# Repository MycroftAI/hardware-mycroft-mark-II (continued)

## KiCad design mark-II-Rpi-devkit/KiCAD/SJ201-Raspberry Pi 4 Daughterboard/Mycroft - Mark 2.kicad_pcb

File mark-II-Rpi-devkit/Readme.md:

# Mycroft Mark II - Prototype Printed Circuit Board

*⛵️ Note that this repository is a work-in-progress. It will be updated and improved on over time.*

This is the first prototype design for the Mark II daughterboard PCB (SJ201).

This board interfaces directly to the Raspberry Pi 4 via the 40-pin GPIO adding a high-quality speaker and microphone array, as well as LEDs and hardware inputs for non-voice interaction and feedback.

The SJ201 can also be used as a USB microphone array with barge-in support. In this configuration the amplifiers do not work as the USB port cannot supply the required power.

The part number SJ201 is derived from Mike’s “Simon Jester” alias in “The Moon is a Harsh Mistress”.

## Major Components
* USB Soundcard (PCM2706)
* Audio Front End (XMOS XVF-3510) - for Microphone input processing
* 20W Amplifier (Maxim Integrated MAX9744)
* 2 Digital MEMS Microphones (ST Micro MP34DT05)
* 12 RGB LEDs (WorldSemi WS2813-MINI)
* 3 momentary buttons (volume up, volume down, action)
* 1 toggle switch (mic mute)

## New Form Factor
There is a new form factor for the Mark II. The new form matches the simplicity to our approach to SJ201 daughterboard. The blocking of the major components is found within the MkII Blocking r2.zip. 

## Our open hardware principles
* **Copy our designs** – build your own Mycroft Mark 2 - Raspberry Pi Edition or its individual parts
* **Modify our designs** – remixing is encouraged
* **Sell products based on our designs** – commercial use is permitted
* **Always keep the open license** – contribute your output back to the community
* **Credit the original author(s)** – like they do in science

## Technical Documentation
For technical details of this board see the [SJ201-Datasheet](SJ201-Datasheet.md).

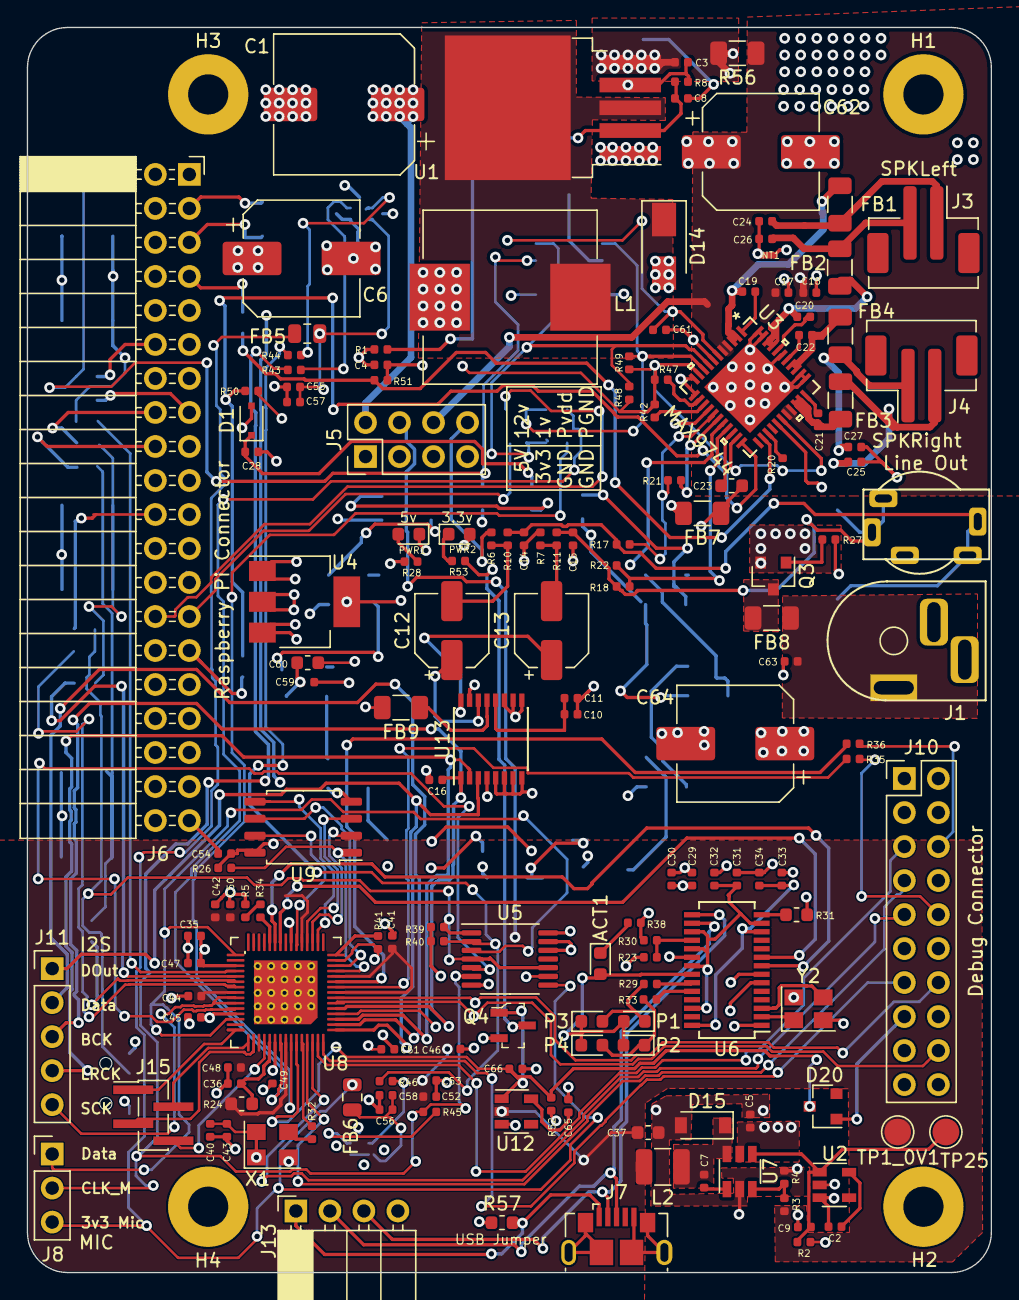
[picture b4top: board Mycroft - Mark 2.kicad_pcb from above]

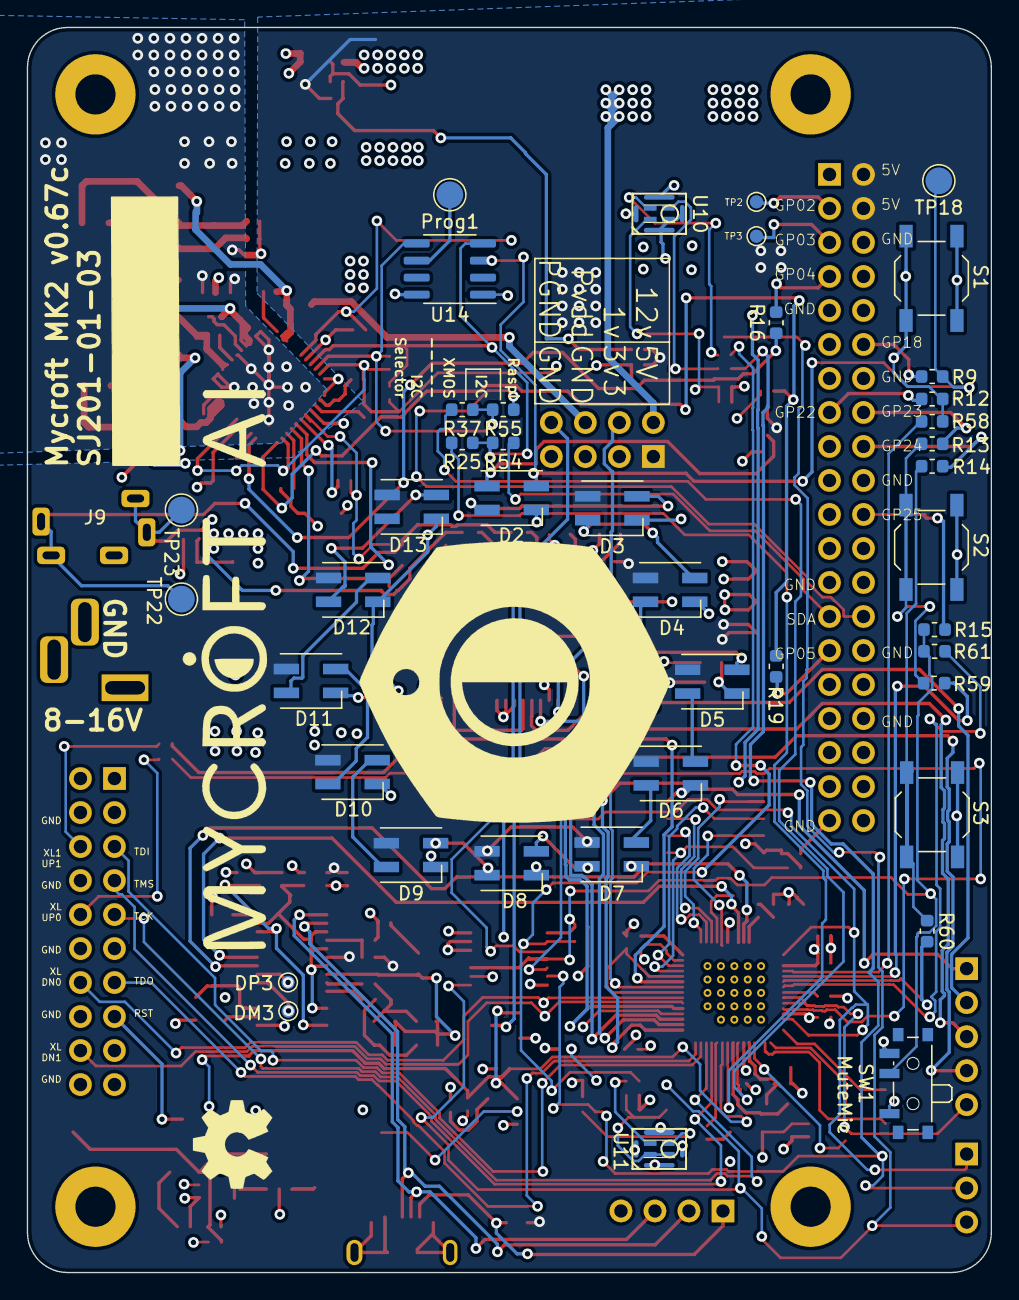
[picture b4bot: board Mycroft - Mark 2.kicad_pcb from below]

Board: 4 copper layers, 72.0 x 93.0 mm, 211 parts (46 on the bottom side), 152 nets.

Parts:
ACT1: LED; LED_0603_1608Metric
C1: 220uF/50V; CP_Elec_10x10
C2, C65: 2.2NF; C_0402_1005Metric
C3, C4, C55, C56, C61: 1uF; C_0402_1005Metric
C5, C11, C30, C32, C34, C59: 10UF; C_0402_1005Metric
C6: 330uF/25V; CP_Elec_8x10.5
C7, C14, C15: 10nF; C_0402_1005Metric
C8: 33NF; C_0402_1005Metric
C9, C66: 1NF; C_0402_1005Metric
C10, C17, C18, C19, C20, C21, C22, C28, C29, C31, C33, C35, C36, C40, C41, C42, C43, C44, C45, C46, C47, C48, C49, C50, C51, C52, C53, C54, C57, C58, C63: 100NF; C_0402_1005Metric
C12, C13: 47UF/16V; CP_Elec_5x5.3
C16: 22pFDNP; C_0402_1005Metric
C23: 2.2UF; C_0603_1608Metric
C24, C25, C26, C27: 470pF; C_0402_1005Metric
C37, C60: 22UF; C_0603_1608Metric
C62, C64: 470UF/16V; CP_Elec_8x10.5
D1: 250mA/100V; D_SOD-323F
D2, D3, D4, D5, D6, D7, D8, D9, D10, D11, D12, D13: WS2812B; LED_WS2812_Mini_3.5x3.5mm_P1.1mm
D14: D_Schottky; D_SMA
D15: D_Schottky; D_SOD-123
D20: BAT54A; SOT-23
DM3: TestPoint; TestPoint_Pad_D1.0mm
DP3: TestPoint; TestPoint_Pad_D1.0mm
FB1, FB2, FB3, FB4, FB7, FB8, FB9: FB; R_1206_3216Metric
FB5, FB6: 1000R; R_0805_2012Metric
H1, H2, H3, H4: MountingHole; MountingHole_3mm_Pad
H5: MountingHole; mycroft_logo_graphic
H6: MountingHole; OSHW-Symbol_6.7x6mm_SilkScreen
H7: MountingHole; mycroft_logo_words
J1: Barrel_Jack; BarrelJack_Vertical
J3, J4: SPK; JST_PH_B2B-PH-SM4-TB_1x02-1MP_P2.00mm_Vertical
J5: PowerTP; PinHeader_2x04_P2.54mm_Vertical
J6: Raspberry_Pi_4; PinSocket_2x20_P2.54mm_Horizontal
J7: USB_B_Micro; USB_Micro-B_GCT_USB3076-30-A
J8: MIC; PinHeader_1x03_P2.54mm_Vertical
J9: AudioJack3_Ground_Switch; STX-3790-5N
J10: Debug Connector; PinHeader_2x10_P2.54mm_Vertical
J11: I2S; PinHeader_1x05_P2.54mm_Vertical
J13: USB-PinHeader; PinSocket_1x04_P2.54mm_Horizontal
J15: Output; PinHeader_1x04_P1.27mm_Vertical_SMD_Pin1Left
L1: 47uH; L_Wuerth_HCI-1365
L2: 2.2UH ±30% 1.55A; L_1210_3225Metric
NT1: Net-Tie_2; NetTie-2_SMD_Pad0.5mm
P1, P2, P3, P4: LED; LED_0603_1608Metric
PWR1, PWR2: LED_RED; LED_0603_1608Metric
Prog1: Prog; TestPoint_Pad_D2.0mm
Q3: AO3401A; SOT-23
Q4: 2N7002; SOT-23-3
R1, R2, R20, R39, R42, R47, R48, R49, R50, R51, R52: 10k; R_0402_1005Metric
R3: 75k; R_0402_1005Metric
R4: 330K; R_0402_1005Metric
R5: 10R; R_0402_1005Metric
R6, R7: 220k; R_0402_1005Metric
R8: 3.3K; R_0402_1005Metric
R9, R12, R13, R14, R15, R16, R19, R54, R55: 0R; R_0603_1608Metric
R10, R11, R43, R44, R45, R46: 100R; R_0402_1005Metric
R17, R18, R21, R22: 20k; R_0402_1005Metric
R23, R26, R40: 47K; R_0402_1005Metric
R24: 4R7; R_0603_1608Metric
R25, R37, R57: 0R - DNP; R_0603_1608Metric
R27, R30: 100k; R_0402_1005Metric
R28: 680R; R_0402_1005Metric
R29, R33, R38, R53: 330R; R_0402_1005Metric
R31: 2.7k; R_0603_1608Metric
R32, R34, R35, R36: 33R; R_0402_1005Metric
R41: 4.7k; R_0402_1005Metric
R56: 0R; R_1206_3216Metric
R58, R59, R60, R61: 0R DNP; R_0603_1608Metric
S1, S2, S3: Button; SW_SPST_TL3342
SW1: MuteMic; SW_SPDT_PCM12
TP1_0V1, TP18, TP22, TP23, TP25: TestPoint; TestPoint_Pad_D2.0mm
TP2, TP3: TestPoint; TestPoint_Pad_D1.0mm
U1: XL4501E1; TO-263-5_TabPin3
U2, U12: NCP303LSN09; SOT-23-5
U3: MAX9744; max9744eth&plus_
U4: NCP565; SOT-223-3_TabPin2
U5: SN74LVC125APWR; TSSOP-14_4.4x5mm_P0.65mm
U6: FE1.1s; SSOP-28_3.9x9.9mm_P0.635mm
U7: MP2359; TSOT-23-6
U8: XMOS-XVF3510; QFN-60-1EP_7x7mm_P0.4mm_EP5.6x5.6mm-HandSolder
U9: AT25SF161 16MBIT; SOIC-8_5.23x5.23mm_P1.27mm
U10, U11: SPK0641HT4H-1; HCLGA-MP34DT05
U13: UDA1334ATS; SSOP-16_4.4x5.2mm_P0.65mm
U14: ATtiny402-SS; SOIC-8_3.9x4.9mm_P1.27mm
X1: SG-210STF 24M; Oscillator_SMD_SeikoEpson_SG8002CE-4Pin_3.2x2.5mm
Y2: 12MHz; Crystal_SMD_3225-4Pin_3.2x2.5mm

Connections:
3.3vHUB: C31.1, C32.2, U6.13, U6.17, U6.19, U6.21, U6.26
12v_Unregulated: C63.1, FB8.1, J1.1
+1V0: C37.1, C41.1, C42.1, C44.1, C46.1, C48.1, C50.1, C52.1, C53.1, J5.4, L2.2, R3.1, R24.2, TP1_0V1.1, U8.8, U8.11, U8.20, U8.27, U8.29, U8.38, U8.48, U8.53, U12.2
+3V3: C35.1, C40.1, C43.1, C45.1, C47.1, C49.1, C51.1, C54.1, C60.1, C61.1, FB9.2, J5.3, PWR2.2, R2.1, R20.1, R26.2, R41.2, R42.1, R47.1, R48.1, R49.1, R50.1, R52.1, SW1.1, U2.2, U3.6, U3.10, U3.21, U3.28, U4.2, U5.9, U5.14, U8.4, U8.14, U8.22, U8.33, U8.42, U8.51, U9.8, U13.4, U14.1, X1.1, X1.4
+5V: C4.1, C5.2, C6.1, C8.1, C29.1, C30.2, C59.1, D1.2, D3.1, D4.1, D5.1, D6.1, D7.1, D8.1, D9.1, D10.1, D11.1, D12.1, D13.1, J5.1, J6.2, J6.4, L1.2, R1.1, R23.2, R28.2, R57.1, U4.3, U6.20, U7.5
+12V: C1.1, C3.1, C64.1, J5.2, Q3.2, R56.2, U1.5
/AudioAmp/ADDR1_3V3: R47.2, U3.13
/AudioAmp/ADDR2_3V3: R42.2, U3.14
/Power/1v0Enable: C9.1, R2.2, TP25.1, U2.1, U7.4
/RaspberryPi/D+: J7.3, J13.2, U6.16
/RaspberryPi/D-: J7.2, J13.3, U6.15
/xmos/3V3_MIC: FB5.2, FB6.2, J8.3, U5.8
/xmos/3V3_MIC0: C55.1, C57.1, FB5.1, U10.VDD
/xmos/3V3_MIC1: C56.1, C58.1, FB6.1, U11.LR, U11.VDD
/xmos/24M: R32.1, U8.56
/xmos/MIC_CLK: U5.5, U8.41
/xmos/MIC_CLK_M: J8.2, R43.1, R45.1, U5.6
/xmos/MIC_DATA: J8.1, U5.3, U8.31, U8.43
/xmos/MIC_DATA_M: R40.2, R44.1, R46.1, U5.2
/xmos/QSPI_CLK: U8.13, U9.6
/xmos/QSPI_CS_N: R26.1, U8.12, U9.1
/xmos/QSPI_D0: U8.17, U9.5
/xmos/QSPI_D1: U8.18, U9.2
/xmos/QSPI_D2: U8.19, U9.3
/xmos/QSPI_D3: U8.21, U9.7
/xmos/TCK: J10.9, U8.58
/xmos/TDI: J10.5, U8.59
/xmos/TDO: J10.13, U8.60
/xmos/TMS: J10.7, U8.57
/xmos/XL_DN0: J10.14, U8.7
/xmos/XL_DN1: J10.18, U8.6
/xmos/XL_UP0: J10.10, R35.2
/xmos/XL_UP1: J10.6, R36.2
ATTinyProg: Prog1.1, U14.6
GND: C1.2, C2.2, C3.2, C4.2, C5.1, C6.2, C9.2, C16.2, C24.2, C25.2, C26.1, C27.1, C28.2, C29.2, C30.1, C31.2, C32.1, C33.2, C34.1, C35.2, C36.2, C37.2, C40.2, C41.2, C42.2, C43.2, C44.2, C45.2, C46.2, C47.2, C48.2, C49.2, C50.2, C51.2, C52.2, C53.2, C54.2, C55.2, C56.2, C57.2, C58.2, C59.2, C60.2, C61.2, C63.2, C64.2, C65.2, C66.2, D2.3, D3.3, D4.3, D5.3, D6.3, D7.3, D8.3, D9.3, D10.3, D11.3, D12.3, D13.3, D14.2, D15.2, FB7.2, J1.2, J1.3, J5.5, J5.7, J6.6, J6.9, J6.14, J6.20, J6.25, J6.30, J6.34, J6.39, J7.5, J7.6, J9.G, J10.4, J10.8, J10.12, J10.16, J10.20, J13.4, NT1.1, PWR1.1, Q4.2, R4.1, R5.2, R8.1, R27.2, R30.2, R31.2, R38.1, R39.2, R40.1, R51.2, S1.2, S2.2, S3.2, SW1.3, U1.1, U1.4, U2.3, U3.7, U3.11, U3.12, U3.15, U3.27, U4.1, U5.7, U5.12, U5.13, U6.1, U7.2, U8.61, U9.4, U10.GND, U10.GND1, U10.GND2, U10.GND3, U10.LR, U11.GND, U11.GND1, U11.GND2, U11.GND3, U12.3, U13.5, U13.6, U13.7, U13.8, U13.9, U13.10, U13.11, U14.8, X1.2, Y2.2, Y2.4
GNDA: C23.2, FB7.1
GPIO4: R16.1, R51.1, U3.24
GPIO5: R19.1, R50.2, U3.22
GPIO18: D2.4, R9.2, TP18.1, U14.3
GPIO22: R12.2, R58.1, S1.1
GPIO23: R13.2, R59.1, S2.1
GPIO24: R14.2, R60.1, S3.1
GPIO25: R15.2, R39.1, R61.1, SW1.2, U5.1, U5.4, U5.10
I2S_BCK: C16.1, J11.3, U8.5, U13.1
I2S_DATA: J11.2, U8.2
I2S_DOUT: J11.1, U8.1, U13.3
I2S_LRCK: J11.4, U8.3, U13.2
I2S_SCK: J11.5, U8.39, U8.40
unnamed: ACT1.1, R38.2
unnamed: ACT1.2, P1.2, P2.2, P3.1, P4.1, U6.22
unnamed: C2.1, U2.5
unnamed: C7.1, D15.1, L2.1, U7.6
unnamed: C7.2, U7.1
unnamed: C8.2, R1.2, R8.2, U1.2
unnamed: C10.1, C11.1, U13.12
unnamed: C12.1, U13.14
unnamed: C12.2, R6.1, R10.2
unnamed: C13.1, U13.16
unnamed: C13.2, R7.1, R11.2
unnamed: C19.1, U3.1
unnamed: C19.2, FB1.2, U3.2, U3.3
unnamed: C20.1, U3.40
unnamed: C20.2, FB2.2, U3.41, U3.42
unnamed: C21.1, U3.33
unnamed: C21.2, FB3.2, U3.31, U3.32
unnamed: C22.1, U3.38
unnamed: C22.2, FB4.2, U3.36, U3.37
unnamed: C23.1, U3.20
unnamed: C24.1, FB1.1, J3.1
unnamed: C25.1, FB3.1, J4.2
unnamed: C26.2, FB2.1, J3.2
unnamed: C27.2, FB4.1, J4.1
unnamed: C28.1, D1.1, D2.1
unnamed: C33.1, C34.2, U6.12, U6.28
unnamed: C36.1, R24.1, U8.50
unnamed: C65.1, U12.5
unnamed: D2.2, D3.4
unnamed: D3.2, D4.4
unnamed: D4.2, D5.4
unnamed: D5.2, D6.4
unnamed: D6.2, D7.4
unnamed: D7.2, D8.4
unnamed: D8.2, D9.4
unnamed: D10.2, D11.4
unnamed: D9.2, D10.4
unnamed: D11.2, D12.4
unnamed: D12.2, D13.4
unnamed: D14.1, L1.1, U1.3
unnamed: D20.1, J10.15
unnamed: DM3.1, U6.6
unnamed: DP3.1, U6.7
unnamed: FB8.2, Q3.3
unnamed: FB9.1, U13.13
unnamed: J6.3, TP2.1
unnamed: J6.5, TP3.1
unnamed: J6.7, R16.2
unnamed: J6.12, R9.1
unnamed: J6.15, R12.1
unnamed: J6.16, R13.1
unnamed: J6.18, R14.1
unnamed: J6.22, R15.1
unnamed: J6.29, R19.2
unnamed: J7.1, J13.1, R57.2
unnamed: P1.1, P3.2, R29.2
unnamed: P2.1, P4.2, R33.2
unnamed: PWR1.2, R28.1
unnamed: PWR2.1, R53.2
unnamed: Q3.1, R27.1
unnamed: Q4.3, R53.1
unnamed: R3.2, R4.2, U7.3
unnamed: R17.2, R21.1, U3.16
unnamed: R18.2, R22.1, U3.19
unnamed: R20.2, U3.25
unnamed: R21.2, U3.17
unnamed: R22.2, U3.18
unnamed: R23.1, R30.1, U6.18
unnamed: R29.1, U6.23
unnamed: R31.1, U6.14
unnamed: R32.2, X1.3
unnamed: R33.1, U6.24
unnamed: R34.1, U8.26
unnamed: R5.1, R34.2
unnamed: R35.1, U8.9
unnamed: R36.1, U8.10
unnamed: R43.2, U10.CLK
unnamed: R44.2, U10.DOUT
unnamed: R45.2, U11.CLK
unnamed: R46.2, U11.DOUT
unnamed: R58.2, U8.34
unnamed: R59.2, U8.35
unnamed: R60.2, U8.36
unnamed: R61.2, U8.37
unnamed: U6.2, Y2.1
unnamed: U6.3, Y2.3
PGND: C10.2, C11.2, C14.1, C15.1, C17.1, C18.1, C62.2, J5.8, NT1.2, R6.2, R7.2, U3.34, U3.35, U3.39, U3.43, U3.44, U3.45, U13.15
PVDD: C17.2, C18.2, C62.1, J5.6, R56.1, U3.4, U3.5, U3.29, U3.30
RST_N: C66.1, D20.3, Q4.1, R52.2, U8.55, U12.1
SCL: R37.1, R49.2, R55.2, U3.9, U14.5
SCL_PI: J6.28, R55.1
SCL_XMOS: R37.2, U8.52
SDA: R25.1, R48.2, R54.2, U3.8, U14.4
SDA_PI: J6.27, R54.1
SDA_XMOS: R25.2, U8.54
SPI_CS_N: R41.1, U8.15
TP1: J15.1, U8.45
TP2: J15.2, U8.46
TP3: J15.3, U8.47
TP4: J15.4, U8.49
USB_XMOS_D_N: U6.8, U8.25
USB_XMOS_D_P: U6.9, U8.24
VoutL: C14.2, J9.T, J9.TN, R10.1, R17.1, TP22.1
VoutR: C15.2, J9.S, J9.SN, R11.1, R18.1, TP23.1

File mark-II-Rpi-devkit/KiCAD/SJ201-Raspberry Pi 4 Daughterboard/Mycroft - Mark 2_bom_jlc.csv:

"Comment","Designator","Footprint","LCSC Part #"
"LED","ACT1","LED_0603_1608Metric","C72043"
"220uF/50V","C1","CP_Elec_10x10","no_part_number"
"2.2NF","C2,C65","C_0402_1005Metric","C1531"
"1uF","C3,C4,C61,C55,C56","C_0402_1005Metric","C52923"
"330uF/25V","C6","CP_Elec_8x10.5","no_part_number"
"10nF","C7,C15,C14","C_0402_1005Metric","C15195"
"33NF","C8","C_0402_1005Metric","C1585"
"1NF","C9,C66","C_0402_1005Metric","C1523"
"47UF/16V","C13,C12","CP_Elec_5x5.3","C134798"
"22pFDNP","C16","C_0402_1005Metric","no_part_number"
"2.2UF","C23","C_0603_1608Metric","C23630"
"470pF","C26,C24,C25,C27","C_0402_1005Metric","C1537"
"10UF","C59,C5,C11,C34,C32,C30","C_0402_1005Metric","C15525"
"22UF","C60,C37","C_0603_1608Metric","C59461"
"100NF","C63,C18,C17,C19,C20,C21,C22,C10,C29,C31,C33,C28,C40,C43,C45,C47,C49,C51,C53,C42,C44,C46,C48,C50,C52,C36,C35,C57,C58,C54,C41","C_0402_1005Metric","C1525"
"470UF/16V","C64,C62","CP_Elec_8x10.5","no_part_number"
"250mA/100V","D1","D_SOD-323F","C2128"
"WS2812B","D13,D9,D2,D12,D11,D10,D3,D4,D5,D6,D7,D8","LED_WS2812_Mini_3.5x3.5mm_P1.1mm","C527089"
"D_Schottky","D14","D_SMA","C22452"
"D_Schottky","D15","D_SOD-123","C8598"
"BAT54A","D20","SOT-23","no_part_number"
"TestPoint","DM3","TestPoint_Pad_D1.0mm","no_part_number"
"TestPoint","DP3","TestPoint_Pad_D1.0mm","no_part_number"
"1000R","FB5,FB6","R_0805_2012Metric","C1017"
"FB","FB8,FB7,FB1,FB2,FB3,FB4,FB9","R_1206_3216Metric","C29107"
"MountingHole","H1,H2,H3,H4","MountingHole_3mm_Pad","no_part_number"
"MountingHole","H5","mycroft_logo_graphic","no_part_number"
"MountingHole","H6","OSHW-Symbol_6.7x6mm_SilkScreen","no_part_number"
"MountingHole","H7","mycroft_logo_words","no_part_number"
"Barrel_Jack","J1","BarrelJack_Vertical","C381117"
"PVDD Jumper","J2","SolderJumper-2_P1.3mm_Bridged_RoundedPad1.0x1.5mm","no_part_number"
"SPKLEFT","J3","JST_PH_B2B-PH-SM4-TB_1x02-1MP_P2.00mm_Vertical","no_part_number"
"SPKRIGHT","J4","JST_PH_B2B-PH-SM4-TB_1x02-1MP_P2.00mm_Vertical","no_part_number"
"PowerTP","J5","PinHeader_2x04_P2.54mm_Vertical","no_part_number"
"Raspberry_Pi_4","J6","PinSocket_2x20_P2.54mm_Horizontal","no_part_number"
"USB_B_Micro","J7","USB_Micro-B_GCT_USB3076-30-A","C319162"
"MIC","J8","PinHeader_1x03_P2.54mm_Vertical","no_part_number"
"AudioJack3_Ground_Switch","J9","STX-3790-5N","no_part_number"
"Debug Connector","J10","PinHeader_2x10_P2.54mm_Vertical","no_part_number"
"I2S","J11","PinHeader_1x05_P2.54mm_Vertical","no_part_number"
"SCL","J12","SolderJumper-3_P1.3mm_Bridged2Bar12_RoundedPad1.0x1.5mm_NumberLabels","no_part_number"
"USB-PinHeader","J13","PinSocket_1x04_P2.54mm_Horizontal","C225512"
"SDA","J14","SolderJumper-3_P1.3mm_Bridged2Bar12_RoundedPad1.0x1.5mm_NumberLabels","no_part_number"
"47uH","L1","L_Wuerth_HCI-1365","C429835"
"2.2UH ±30% 1.55A","L2","L_1210_3225Metric","C86074"
"Net-Tie_2","NT1","NetTie-2_SMD_Pad0.5mm","no_part_number"
"LED","P1,P3,P2,P4","LED_0603_1608Metric","C72043"
"Prog","Prog1","TestPoint_Pad_D2.0mm","no_part_number"
"LED_RED","PWR1,PWR2","LED_0603_1608Metric","C2286"
"AO3401A","Q3","SOT-23","C15127"
"2N7002","Q4","SOT-23-3","C8545"
"10k","R1,R2,R20,R47,R42,R49,R48,R50,R51,R52,R39","R_0402_1005Metric","C25744"
"75k","R3","R_0402_1005Metric","C25798"
"330K","R4","R_0402_1005Metric","C25778"
"10R","R5","R_0402_1005Metric","C25077"
"220k","R7,R6","R_0402_1005Metric","C25767"
"3.3K","R8","R_0402_1005Metric","C25890"
"100R","R11,R10,R43,R44,R45,R46","R_0402_1005Metric","C25076"
"20k","R21,R22,R17,R18","R_0402_1005Metric","C25765"
"47K","R23,R26,R40","R_0402_1005Metric","C25792"
"4R7","R24","R_0603_1608Metric","C23164"
"100k","R27,R30","R_0402_1005Metric","C25741"
"680R","R28","R_0402_1005Metric","C25130"
"330R","R29,R33,R38,R53","R_0402_1005Metric","C25104"
"2.7k","R31","R_0603_1608Metric","C13167"
"33R","R34,R36,R35,R32","R_0402_1005Metric","C25105"
"4.7k","R41","R_0402_1005Metric","C25900"
"Action","S1","SW_SPST_TL3342","C318884"
"VolUp","S2","SW_SPST_TL3342","C318884"
"VolDown","S3","SW_SPST_TL3342","C318884"
"MuteMic","SW1","SW_SPDT_PCM12","C221841"
"TestPoint","TP1_0V1","TestPoint_Pad_D2.0mm","no_part_number"
"TestPoint","TP2,TP3","TestPoint_Pad_D1.0mm","no_part_number"
"TestPoint","TP25,TP23,TP22,TP18","TestPoint_Pad_D2.0mm","no_part_number"
"XL4501E1","U1","TO-263-5_TabPin3","C73025"
"NCP303LSN09","U2,U12","SOT-23-5","C150075"
"MAX9744","U3","max9744eth&plus_","no_part_number"
"AMS1117-3.3","U4","SOT-223-3_TabPin2","C6186"
"SN74LVC125APWR","U5","TSSOP-14_4.4x5mm_P0.65mm","C7813"
"FE1.1s","U6","SSOP-28_3.9x9.9mm_P0.635mm","C9359"
"MP2359","U7","TSOT-23-6","C14259"
"XMOS-XVF3510","U8","QFN-60-1EP_7x7mm_P0.4mm_EP5.6x5.6mm-HandSolder","no_part_number"
"AT25SF161 16MBIT","U9","SOIC-8_5.23x5.23mm_P1.27mm","C93710"
"SPK0641HT4H-1","U10,U11","HCLGA-MP34DT05","no_part_number"
"UDA1334ATS","U13","SSOP-16_4.4x5.2mm_P0.65mm","C494494"
"ATtiny402-SS","U14","SOIC-8_3.9x4.9mm_P1.27mm","no_part_number"
"USB Jumper","USB_Power1","SolderJumper-2_P1.3mm_Open_TrianglePad1.0x1.5mm","no_part_number"
"SG-210STF 24M","X1","Oscillator_SMD_SeikoEpson_SG8002CE-4Pin_3.2x2.5mm","C32528"
"12MHz","Y2","Crystal_SMD_3225-4Pin_3.2x2.5mm","C9002"

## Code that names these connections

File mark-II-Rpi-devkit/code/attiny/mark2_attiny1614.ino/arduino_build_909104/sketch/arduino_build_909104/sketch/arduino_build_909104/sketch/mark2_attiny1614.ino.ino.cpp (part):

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byte bufferI2C[256];
byte pattern[NUMPATTERNS][NUMPIXELS];

// When we setup the NeoPixel library, we tell it how many pixels, and which pin to use to send signals.
// Note that for older NeoPixel strips you might need to change the third parameter--see the strandtest
// example for more information on possible values. Finally, for the 4th argument we pass the array we
// defined above.
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//volatile byte state = 1;


#define TPU_RST_L   8   //PA1
#define TPU_PGOOD   9   //PA2
#define FAN_TACH    10  //PA3
#define FAN_PWM     0   //PA4

#define TPU_PMIC_EN 2   //PA6
#define GPIO_PA7    3   //PA7

volatile byte state   = 0;
long lastButtonPress = 0;
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  Wire.onReceive(receiveEvent); // register event
  Wire.onRequest(requestEvent);
  pinMode(NEOXPIXELPIN,OUTPUT);
  pinMode(FAN_PWM  ,   OUTPUT);
  pinMode(FAN_TACH ,   INPUT); 
  pinMode(TPU_PGOOD,   INPUT);
  pinMode(TPU_PMIC_EN, OUTPUT);
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
  // FAN_PWM at zero turns on Fan
  // invert input so 255 is full on, zero is off
  analogWrite(FAN_PWM, constrain(255 - fanSpeed, 0, 255));

}
inline void setState(byte s1){
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
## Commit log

2020-01-28 Create BOM
2020-01-28 Update BOM
2020-01-30 Rename instructions.md to Instructions.md
2020-01-30 Create STL
2020-01-30 Create STP
2020-01-30 Rename STP to STP.md
2020-01-30 Rename STL to STL.md
2020-07-14 Create mark-II-Rpi-OTS
2020-07-14 reorganizing files
    Renamed repo to hard-ware-mycroft-mark-II to encompass all Mark II hardware projects, and renamed Mark-II-rpi-prototype to Mark-II-rpi-ots. Created mark-II-rpi-devkit for the current raspberry pi bas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
2020-07-14 Initial Design
2020-07-15 Replace SMD 40pin header, replace with Thru Hole version
2020-07-15 update version number
    update version number
2020-07-15 add repo overview
2020-07-15 cleanup and shift info to component dir
2020-07-15 fix image paths
2020-07-15 add call for feedback
2020-07-15 fix broken link
2020-07-15 Update BOM - fix OPL numbers for Seeed PCBA
2020-07-15 fix library so only using 0.3mm drill and bigger
2020-07-22 Updated KiCAD files to 0.63 for PCB printing & Assembly at JLCPCB
2020-07-22 Add updated PCB Renders
2020-07-24 Change USB IC to CM108B, add in Line Out jack, prep for 2 PCB sandwich
2020-07-24 Change vertical barrel connector, files sent to JLC PCB for printing and assembly.
2020-07-24 Update Readme with renders
2020-08-08 Mark 2 - PCB Files to the printer
2020-08-17 Update to v0.66 - printed at JLC - 2nd spin
2020-08-29 Fix missing library path
2020-08-29 Fix missing items in schematic in Github
2020-08-29 Fix missing items in schematic in Github - add in libraries
2020-09-04 Add in USB Adapter - SJ-202
2020-09-09 Update part numbers and links
2020-09-16 Add in testing scripts for SJ-201
2020-09-27 SJ201 - Removed CM108b soundcard, added in I2S to Line out, ATTin402. Moved holes in layout. SJ202 - extened length to plug into USB2.0 port
2020-09-27 SJ201 Move BOM files into BOM folder
2020-10-08 SJ-201 v3, sent to PCB Fab. Removed USB Hub, add in I2S to Line Out
2020-10-08 SJ-202 USB Jumper Update & Readme updates
2020-10-08 Readme updates
2020-11-20 Rev4 Update - Add in Coral TPU, TAS5806, remove I2S * MAX9744. Change Attiny to Attin1614
2020-11-23 Rev4 Update - fix some wiring, export for printing Rev 4
2020-12-11 Update README.md
    fix images
2020-12-11 Update README.md
    Updated for Rev 4 board specs.
2020-12-12 Update README.md
    Updated (partially) for R4
2020-12-30 add standard license and move to subdirectory
2021-01-02 SJ-201-R6 for FAB - removed buffer IC
2021-02-19 Update eeprom_update.sh
    2021-02-19 - J.M. - Improved Docs
2021-03-04 Updated files for R6 v2
2021-03-04 deprecated OTS HW
2021-03-04 deprecated this design
2021-03-04 removed USB mode
    The USB on the Pi 4 was unreliable for real-time audio data.
2021-03-04 Updated to match version 6.02.
    Also removed part numbering and "related parts" sections.
2021-03-04 not used in Rev 6 design
2021-03-04 removed WIP note
2021-03-04 Added in test jig scripts, update ATTiny Code
2021-03-04 Remove extra images folder, add in Gerbers
2021-03-04 Update Reference Files, remove unused parts
2021-03-05 Update part datasheet for 12v power to 5v
2021-03-05 Rename readme to readme.md
2021-03-08 Cleaned up SJ201 directory
2021-03-08 Removed unused files, cleaned up directory, remove SJ202
2021-03-08 Add back Readme
2021-03-08 Bugfix
2021-03-08 Removed redundant files
2021-03-09 fix dependency issue
2021-03-14 Update libraries, reorganize files
2021-03-18 Create MkII SJ240 SW19 r9.zip
    Added Zip containing STEP files of the SJ240 R9 enclosure
2021-03-19 Bump pillow from 7.1.2 to 8.1.1 in /mark-II-Rpi-devkit/code/TestingJig
    Bumps [pillow](https://github.com/python-pillow/Pillow) from 7.1.2 to 8.1.1.
    - [Release notes](https://github.com/python-pillow/Pillow/releases)
    - [Changelog](https://github.com/python-pillow/Pillow/blob/master/CHANGES.rst)
    - [Commits](https://github.com/python-pillow/Pillow/compare/7.1.2...8.1.1)
2021-06-02 Bump urllib3 in /mark-II-Rpi-devkit/code/TestingJig
    Bumps [urllib3](https://github.com/urllib3/urllib3) from 1.24.3 to 1.26.5.
    - [Release notes](https://github.com/urllib3/urllib3/releases)
    - [Changelog](https://github.com/urllib3/urllib3/blob/main/CHANGES.rst)
    - [Commits](https://github.com/urllib3/urllib3/compare/1.24.3...1.26.5)
    ---
    updated-dependencies:
2021-06-08 Bump pillow from 7.1.2 to 8.2.0 in /mark-II-Rpi-devkit/code/TestingJig
    Bumps [pillow](https://github.com/python-pillow/Pillow) from 7.1.2 to 8.2.0.
    - [Release notes](https://github.com/python-pillow/Pillow/releases)
    - [Changelog](https://github.com/python-pillow/Pillow/blob/master/CHANGES.rst)
    - [Commits](https://github.com/python-pillow/Pillow/compare/7.1.2...8.2.0)
    ---
    updated-dependencies:
2021-09-08 Bump pillow from 7.1.2 to 8.3.2 in /mark-II-Rpi-devkit/code/TestingJig
    Bumps [pillow](https://github.com/python-pillow/Pillow) from 7.1.2 to 8.3.2.
    - [Release notes](https://github.com/python-pillow/Pillow/releases)
    - [Changelog](https://github.com/python-pillow/Pillow/blob/master/CHANGES.rst)
    - [Commits](https://github.com/python-pillow/Pillow/compare/7.1.2...8.3.2)
    ---
    updated-dependencies:
2021-10-21 Bump babel from 2.9.0 to 2.9.1 in /mark-II-Rpi-devkit/code/TestingJig
    Bumps [babel](https://github.com/python-babel/babel) from 2.9.0 to 2.9.1.
    - [Release notes](https://github.com/python-babel/babel/releases)
    - [Changelog](https://github.com/python-babel/babel/blob/master/CHANGES)
    - [Commits](https://github.com/python-babel/babel/compare/v2.9.0...v2.9.1)
    ---
    updated-dependencies:
2021-11-08 MII AC spacer
    Added AC Spacer for SJ240 3D printed design
2021-11-11 Update checklist for SJ-201-R7
2021-12-07 Added Speaker Spacer for alternate speaker driver
2021-12-07 Audio Chamber for SJ230 (laser cut enclosure)
2022-01-13 Bump pillow from 7.1.2 to 9.0.0 in /mark-II-Rpi-devkit/code/TestingJig
    Bumps [pillow](https://github.com/python-pillow/Pillow) from 7.1.2 to 9.0.0.
    - [Release notes](https://github.com/python-pillow/Pillow/releases)
    - [Changelog](https://github.com/python-pillow/Pillow/blob/main/CHANGES.rst)
    - [Commits](https://github.com/python-pillow/Pillow/compare/7.1.2...9.0.0)
    ---
    updated-dependencies:
2022-02-25 Revision 8 changes
    remove I2S headphone output jack
2022-03-12 Bump pillow from 7.1.2 to 9.0.1 in /mark-II-Rpi-devkit/code/TestingJig
    Bumps [pillow](https://github.com/python-pillow/Pillow) from 7.1.2 to 9.0.1.
    - [Release notes](https://github.com/python-pillow/Pillow/releases)
    - [Changelog](https://github.com/python-pillow/Pillow/blob/main/CHANGES.rst)
    - [Commits](https://github.com/python-pillow/Pillow/compare/7.1.2...9.0.1)
    ---
    updated-dependencies:
2022-05-25 Bump pyjwt from 1.7.1 to 2.4.0 in /mark-II-Rpi-devkit/code/TestingJig
    Bumps [pyjwt](https://github.com/jpadilla/pyjwt) from 1.7.1 to 2.4.0.
    - [Release notes](https://github.com/jpadilla/pyjwt/releases)
    - [Changelog](https://github.com/jpadilla/pyjwt/blob/master/CHANGELOG.rst)
    - [Commits](https://github.com/jpadilla/pyjwt/compare/1.7.1...2.4.0)
    ---
    updated-dependencies:
2022-06-22 Bump numpy from 1.20.1 to 1.22.0 in /mark-II-Rpi-devkit/code/TestingJig
    Bumps [numpy](https://github.com/numpy/numpy) from 1.20.1 to 1.22.0.
    - [Release notes](https://github.com/numpy/numpy/releases)
    - [Changelog](https://github.com/numpy/numpy/blob/main/doc/HOWTO_RELEASE.rst)
    - [Commits](https://github.com/numpy/numpy/compare/v1.20.1...v1.22.0)
    ---
    updated-dependencies:
2022-06-28 Bump arrow from 0.12.0 to 0.15.1 in /mark-II-Rpi-devkit/code/TestingJig
    Bumps [arrow](https://github.com/arrow-py/arrow) from 0.12.0 to 0.15.1.
    - [Release notes](https://github.com/arrow-py/arrow/releases)
    - [Changelog](https://github.com/arrow-py/arrow/blob/master/CHANGELOG.rst)
    - [Commits](https://github.com/arrow-py/arrow/compare/0.12.0...0.15.1)
    ---
    updated-dependencies:
2022-09-23 Add SJ240 3D print files
    The SJ240 is the 3D printed enclosure.
    These STL files can be used to print an enclosure for the Mark II Dev Kit.
    Note that screws and threaded inserts are also required.
2022-09-23 Add info on 3D print files
    Includes link to appropriate threaded inserts
2022-09-23 Add link to Instructables for 3D printed case
2022-09-23 Bump protobuf in /mark-II-Rpi-devkit/code/TestingJig
    Bumps [protobuf](https://github.com/protocolbuffers/protobuf) from 3.15.2 to 3.18.3.
    - [Release notes](https://github.com/protocolbuffers/protobuf/releases)
    - [Changelog](https://github.com/protocolbuffers/protobuf/blob/main/generate_changelog.py)
    - [Commits](https://github.com/protocolbuffers/protobuf/compare/v3.15.2...v3.18.3)
    ---
    updated-dependencies:
2022-10-22 SJ-201-R10
2022-10-25 BOM for SJ-201-R10
2022-11-22 Bump pillow from 7.1.2 to 9.3.0 in /mark-II-Rpi-devkit/code/TestingJig
    Bumps [pillow](https://github.com/python-pillow/Pillow) from 7.1.2 to 9.3.0.
    - [Release notes](https://github.com/python-pillow/Pillow/releases)
    - [Changelog](https://github.com/python-pillow/Pillow/blob/main/CHANGES.rst)
    - [Commits](https://github.com/python-pillow/Pillow/compare/7.1.2...9.3.0)
    ---
    updated-dependencies:
2022-12-08 Bump certifi in /mark-II-Rpi-devkit/code/TestingJig
    Bumps [certifi](https://github.com/certifi/python-certifi) from 2020.12.5 to 2022.12.7.
    - [Release notes](https://github.com/certifi/python-certifi/releases)
    - [Commits](https://github.com/certifi/python-certifi/compare/2020.12.05...2022.12.07)
    ---
    updated-dependencies:
    - dependency-name: certifi
2023-02-08 Bump cryptography in /mark-II-Rpi-devkit/code/TestingJig
    Bumps [cryptography](https://github.com/pyca/cryptography) from 3.4.6 to 39.0.1.
    - [Release notes](https://github.com/pyca/cryptography/releases)
    - [Changelog](https://github.com/pyca/cryptography/blob/main/CHANGELOG.rst)
    - [Commits](https://github.com/pyca/cryptography/compare/3.4.6...39.0.1)
    ---
    updated-dependencies:
2023-02-20 Create MkII SJ250 ASSEM r6.zip
    Mark II production mechanical CAD full assembly in STEP format
2023-02-24 add body assembly instructions
2023-02-24 add images for body assembly
2023-02-24 remove unusable sizing parameters from images
2023-02-24 add breaks before and after images
2023-02-24 upload top, speaker and display assembly images
2023-02-24 formatting tweaks to top assembly instructions
2023-02-24 add speaker and display assembly instructions
2023-02-24 correct image links
2023-02-24 Rename mark-ii-assembly.md to README.md
2023-06-13 Added KiCAD layout file
